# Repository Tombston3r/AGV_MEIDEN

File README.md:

# AGV MEIDEN

Deux chantiers sur le même chariot filoguidé MEIDEN (carte d'origine
`AIO AGV Control V5.0.1`) :

Toutes les architectures suivent la **même chaîne** depuis le 2026-08-28 :

```
Boutons d'appel (optionnels) -> Poste Central -> Carte AGV Control -> AGV
                                API planning
                                appels
```

Les boutons sont **optionnels** : le planning seul fait rouler l'AGV. Les trois
architectures ne diffèrent plus que par la **liaison du poste vers l'AGV** :
[`docs/ARCHITECTURE_COMMUNE.md`](docs/ARCHITECTURE_COMMUNE.md).

| Dossier | Chantier | État |
|---|---|---|
| [`Comm distance/`](Comm%20distance/) | **Remplacement du système d'appel** : 4 architectures étudiées (cellulaire, hybride, LoRa, Wi-Fi), bancs d'essai, matériel KiCad | 470 tests verts, choix client non tranché |
| [`Timer/`](Timer/) | **Planning journalier** : missions déclenchées sur horloge, validation quotidienne par l'opérateur | moteur livré, 18 tests verts |

Chaque chantier porte son `README.md` **et** son `DEPLOY.md`, à quoi ça sert
d'un côté, comment le mettre en service et ce qu'on doit voir de l'autre. La
règle de rangement commune est dans
[`docs/ORGANISATION.md`](docs/ORGANISATION.md) : *tout ce qui sert à une chose
vit avec elle, documentation comprise.*

Toutes les interfaces web du dépôt suivent le **même thème** : fond blanc,
bleu outremer, logo AIO : [`docs/theme/`](docs/theme/), propagé par
`outils/theme.sh`.

Les deux partagent la même carte et le même cœur métier : le Timer produira
ses missions vers le séquenceur déjà écrit dans
[`Comm distance/architectures/A3_Wifi/`](Comm%20distance/architectures/A3_Wifi/).

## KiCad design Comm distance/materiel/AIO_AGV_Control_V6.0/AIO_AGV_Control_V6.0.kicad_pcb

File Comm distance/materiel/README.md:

# Matériel : projets KiCad

**Une carte, un projet, un seul endroit.** Même quand deux architectures
partagent une carte, elle n'est pas dupliquée : trois copies divergentes de la
V6.0 ont déjà coexisté dans ce dépôt, et il a fallu comparer les schémas pour
savoir laquelle portait le travail réel. Un firmware dupliqué se compare par
`diff` ; deux schémas KiCad divergents, non.

| Projet | Sert à | Empreintes | État |
|---|---|---:|---|
| [`AIO_AGV_Control_V5.0.1/`](AIO_AGV_Control_V5.0.1/) | **A3** : Wi-Fi | 57 | carte d'origine, **en service sur le chariot** |
| [`AIO_AGV_Control_V6.0/`](AIO_AGV_Control_V6.0/) | **A2** et **A3** : LoRa | 59 | Gerbers exportés |

## Ce qui distingue la V6.0

Le diff des deux projets ne montre **aucun écart** hors la radio : mêmes
`Mega2560 Pro` et `ESP32-DEVKITC`, mêmes 23 `IRF520` et résistances de grille,
même `L7806CV`, même `TDN 5-2411WISM`, mêmes SUB-D 25.

S'y ajoutent un **`RFM95W-868S2` (U2)** et son **embase coaxiale (J3)**.

### Brochage relevé

| RFM95W | ESP32 |
|---|---|
| `NSS` | `IO5` |
| `SCK` | `IO18` |
| `MISO` | `IO19` |
| `MOSI` | `IO23` |
| `DIO0` | `IO26` |

⚠️ **`RESET` (pad 6) n'est pas connectée.** Aucun reset logiciel n'est possible :
un module figé ne se récupérera qu'en coupant l'alimentation de la carte.
**`IO27` est libre** et conviendrait, sans fonction de strapping au démarrage,
contrairement à `IO0`, `IO2`, `IO12` ou `IO15`.

⚠️ **`IO16` et `IO17` sont réservées** : elles portent la liaison série vers le
`Mega2560 Pro`, via un pont diviseur 2,2 k / 4,7 k dans le sens 5 V → 3,3 V.

## Points relevés sur la V5.0.1, valables pour les deux

- **Les trois UART matériels du MEGA sont inutilisables** : leurs broches de
  réception portent `Y13` (D19), `Y11` (D17) et `Y05` (D15). La liaison
  inter-microcontrôleurs est en `SoftwareSerial` sur D52/D53, à 38 400 bauds.
- **L'`IRF520` n'est pas un MOSFET logic-level** : seuil spécifié de 2 à 4 V,
  `Rds(on)` garanti à Vgs = 10 V. Attaqué en 5 V il conduit, mais hors des
  conditions du constructeur. L'`IRL520N` est la version logic-level **au même
  brochage**.
- **Les 21 entrées Y arrivent directement sur les broches de l'ATmega**, sans
  protection. Le client a vérifié que les niveaux le permettent.

Le relevé complet du câblage SUB-D vit dans
[`../architectures/A3_Wifi/docs/subd25_atmega.md`](../architectures/A3_Wifi/docs/subd25_atmega.md).

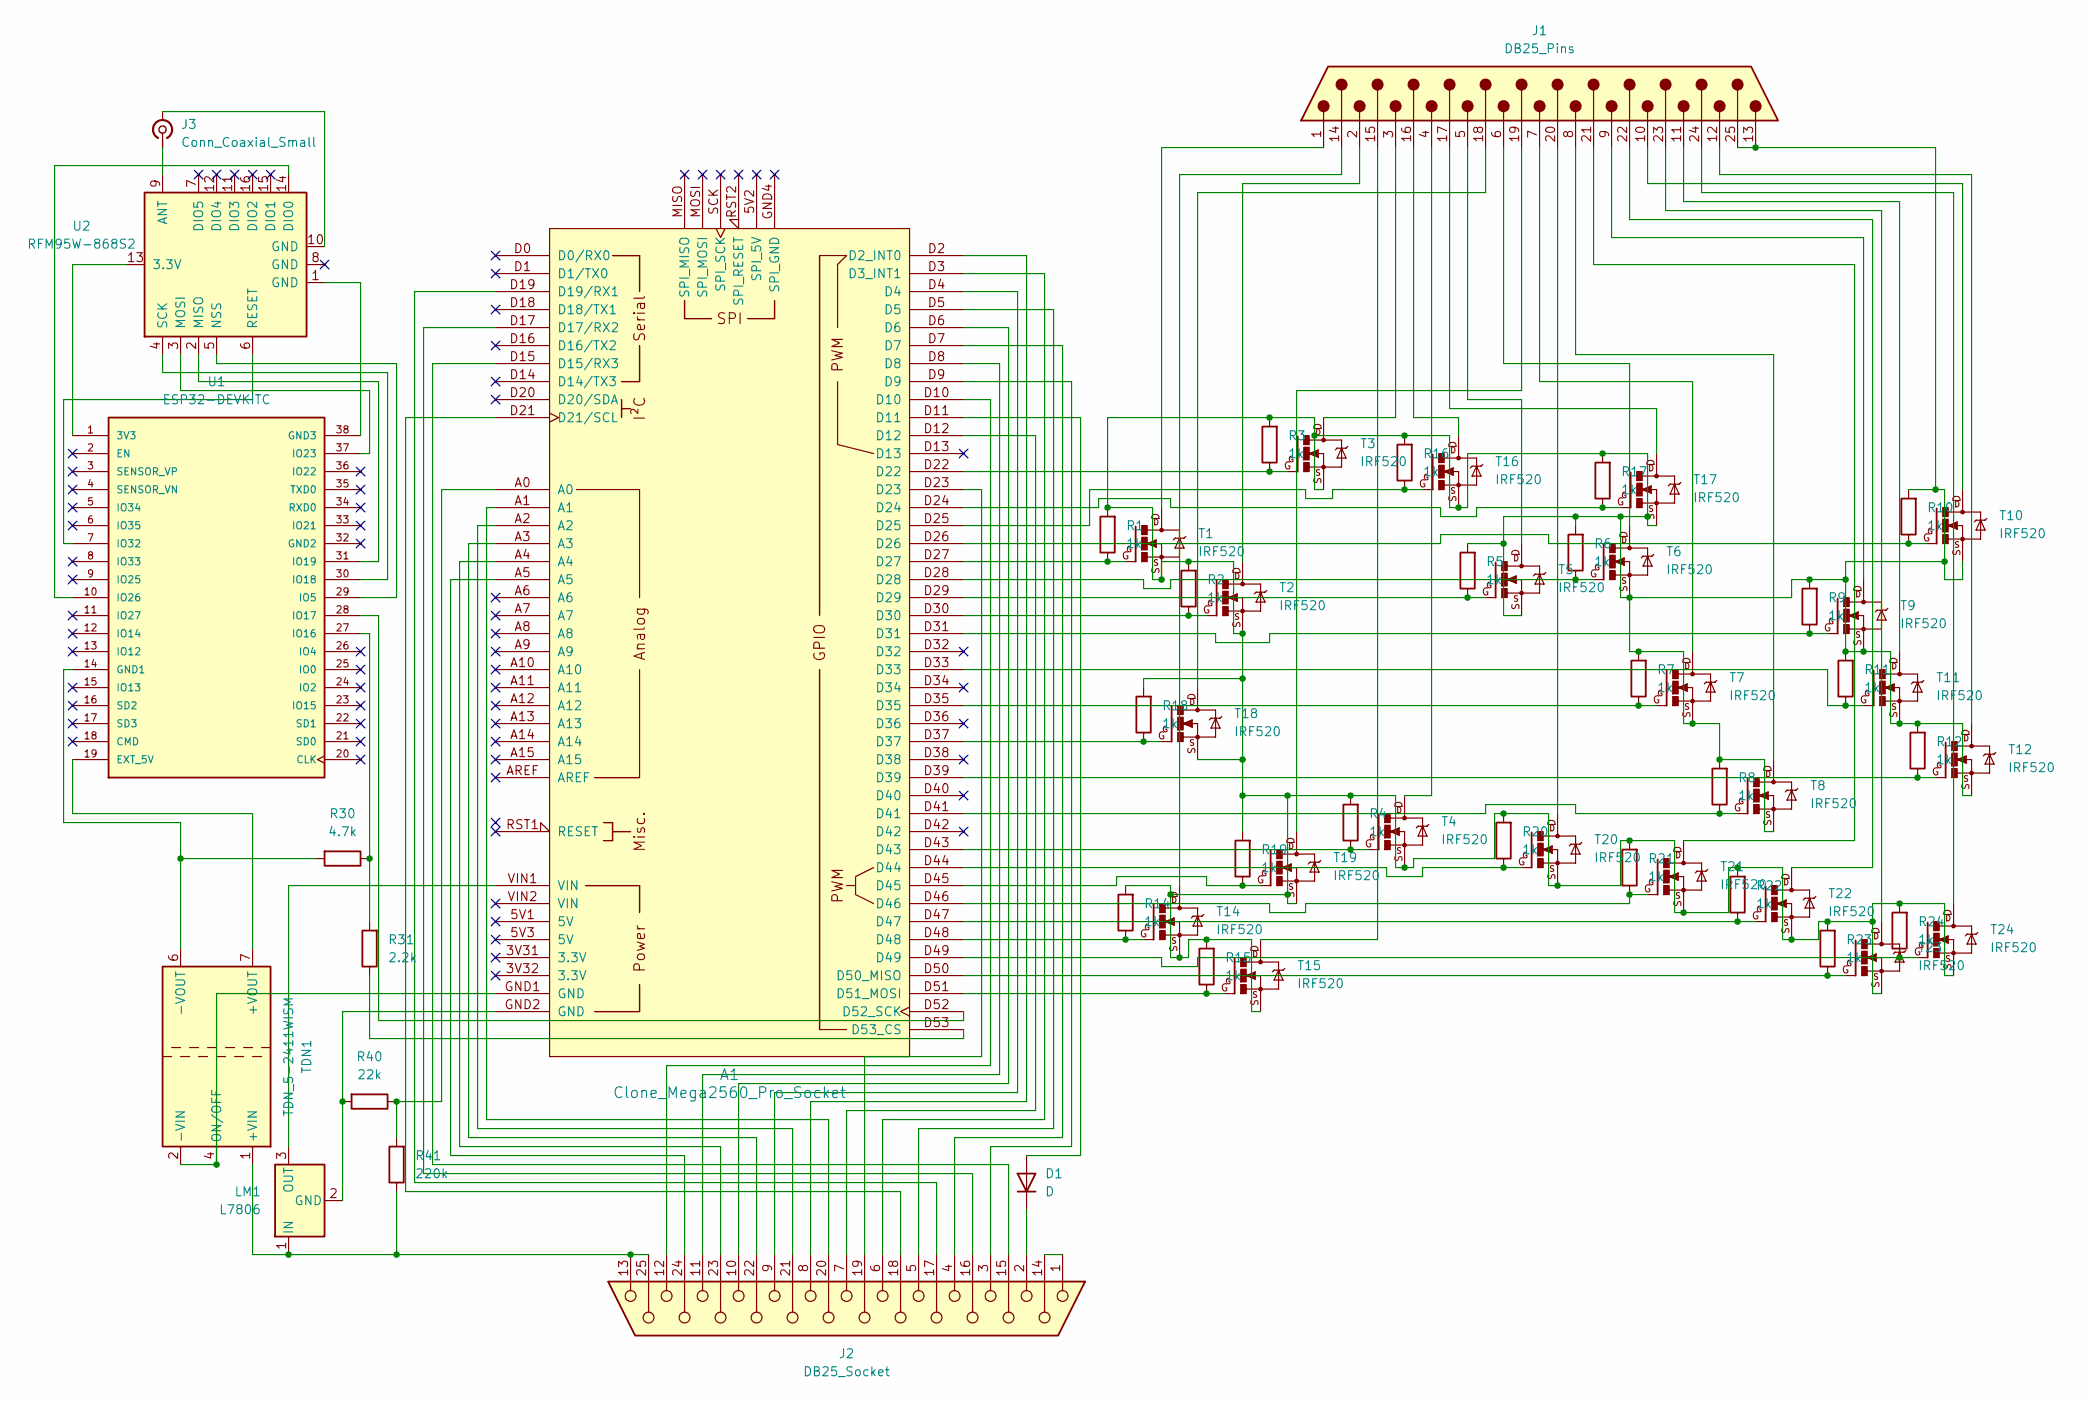
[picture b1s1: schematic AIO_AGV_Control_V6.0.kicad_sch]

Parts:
A1: Clone_Mega2560_Pro_Socket
D1: D; D_DO-41_SOD81_P10.16mm_Horizontal
J1: DB25_Pins; AMPHENOL_DB25P564CTXLF
J2: DB25_Socket; AMPHENOL_DB25S564GTLF
J3: Conn_Coaxial_Small; SMA_Amphenol_901-143_Horizontal
LM1: L7806; TO255P1020X450X1968-3B
R1, R2, R3, R4, R5, R6, R7, R8, R9, R10, R11, R12, R14, R15, R16, R17, R18, R19, R20, R21, R22, R23, R24: 1k; R_Axial_DIN0411_L9.9mm_D3.6mm_P12.70mm_Horizontal
R30: 4.7k; R_Axial_DIN0411_L9.9mm_D3.6mm_P12.70mm_Horizontal
R31: 2.2k; R_Axial_DIN0411_L9.9mm_D3.6mm_P12.70mm_Horizontal
R40: 22k; R_Axial_DIN0411_L9.9mm_D3.6mm_P12.70mm_Horizontal
R41: 220k; R_Axial_DIN0411_L9.9mm_D3.6mm_P12.70mm_Horizontal
T1, T2, T3, T4, T5, T6, T7, T8, T9, T10, T11, T12, T14, T15, T16, T17, T18, T19, T20, T21, T22, T23, T24: IRF520; TO220BV
TDN1: TDN_5-2411WISM; Converter_DCDC_TRACO_TDN_5-xxxxWISM_SMD
U1: ESP32-DEVKITC; MODULE_ESP32-DEVKITC; PARTREV N/A
U2: RFM95W-868S2; HOPERF_RFM9XW_SMD

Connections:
unnamed: A1.D2 (D2_INT0), J2.8
unnamed: A1.D3 (D3_INT1), J2.6
unnamed: A1.D15 (D15/RX3), J2.15
unnamed: A1.D17 (D17/RX2), J2.16
unnamed: A1.D19 (D19/RX1), J2.17
unnamed: A1.D21 (D21/SCL), J2.18
unnamed: A1.D50 (D50_MISO), R23.1, T23.G
unnamed: A1.D51 (D51_MOSI), R15.1, T15.G
unnamed: A1.D52 (D52_SCK), U1.28 (IO17)
unnamed: A1.D53 (D53_CS), R31.1
unnamed: A1.A0, R40.1, R41.2
unnamed: A1.D4, J2.9
unnamed: A1.D5, J2.5
unnamed: A1.D6, J2.10
unnamed: A1.D7, J2.4
unnamed: A1.D8, J2.11
unnamed: A1.D9, J2.3
unnamed: A1.D10, J2.12
unnamed: A1.D12, J2.7
unnamed: A1.D22, R3.1, T3.G
unnamed: A1.D24, R17.1, T17.G
unnamed: A1.D25, R16.1, T16.G
unnamed: A1.D26, R10.1, T10.G
unnamed: A1.D27, R1.1, T1.G
unnamed: A1.D28, R6.1, T6.G
unnamed: A1.D29, R5.1, T5.G
unnamed: A1.D30, R2.1, T2.G
unnamed: A1.D31, R9.1, T9.G
unnamed: A1.D33, R11.1, T11.G
unnamed: A1.D35, R7.1, T7.G
unnamed: A1.D37, R18.1, T18.G
unnamed: A1.D39, R12.1, T12.G
unnamed: A1.D41, R8.1, T8.G
unnamed: A1.D43, R4.1, T4.G
unnamed: A1.D44, R20.1, T20.G
unnamed: A1.D45, R19.1, T19.G
unnamed: A1.D46, R21.1, T21.G
unnamed: A1.D47, R22.1, T22.G
unnamed: A1.D48, R14.1, T14.G
unnamed: A1.D49, R24.1, T24.G
unnamed: A1.D11, D1.2 (A)
unnamed: D1.1 (K), J2.2
unnamed: J1.14, T14.D
unnamed: J1.15, T15.D
unnamed: J1.16, T16.D
unnamed: J1.17, T17.D
unnamed: J1.18, T18.D
unnamed: J1.19, T19.D
unnamed: J1.20, T20.D
unnamed: J1.21, T21.D
unnamed: J1.22, T22.D
unnamed: J1.23, T23.D
unnamed: J1.24, T24.D
unnamed: J1.13, J1.25, R1.2, R2.2, R3.2, R4.2, R5.2, R6.2, R7.2, R8.2, R9.2, R10.2, R11.2, R12.2, R14.2, R15.2, R16.2, R17.2, R18.2, R19.2, R20.2, R21.2, R22.2, R23.2, R24.2, T1.S, T2.S, T3.S, T4.S, T5.S, T6.S, T7.S, T8.S, T9.S, T10.S, T11.S, T12.S, T14.S, T15.S, T16.S, T17.S, T18.S, T19.S, T20.S, T21.S, T22.S, T23.S, T24.S
unnamed: J1.1, T1.D
unnamed: J1.2, T2.D
unnamed: J1.3, T3.D
unnamed: J1.4, T4.D
unnamed: J1.5, T5.D
unnamed: J1.6, T6.D
unnamed: J1.7, T7.D
unnamed: J1.8, T8.D
unnamed: J1.9, T9.D
unnamed: J1.10, T10.D
unnamed: J1.11, T11.D
unnamed: J1.12, T12.D
unnamed: J2.1, J2.14
unnamed: A1.D23, J2.19
unnamed: A1.A1, J2.20
unnamed: A1.A2, J2.21
unnamed: A1.A3, J2.22
unnamed: A1.A4, J2.23
unnamed: A1.A5, J2.24
unnamed: J2.13, J2.25, LM1.1 (IN), R41.1, TDN1.1 (+VIN)
unnamed: J3.2 (Ext), U2.10 (GND)
unnamed: J3.1 (In), U2.9 (ANT)
unnamed: A1.GND2 (GND), LM1.2 (GND), R40.2
unnamed: A1.VIN1 (VIN), LM1.3 (OUT)
unnamed: TDN1.7 (+VOUT), U1.19 (EXT_5V)
unnamed: A1.GND1 (GND), TDN1.2 (-VIN), TDN1.4 (ON/OFF)
unnamed: R30.2, TDN1.6 (-VOUT), U1.14 (GND1)
unnamed: U1.1 (3V3), U2.13 (3.3V)
unnamed: U1.38 (GND3), U2.1 (GND)
unnamed: U1.29 (IO5), U2.5 (NSS)
unnamed: R30.1, R31.2, U1.27 (IO16)
unnamed: U1.30 (IO18), U2.4 (SCK)
unnamed: U1.31 (IO19), U2.2 (MISO)
unnamed: U1.37 (IO23), U2.3 (MOSI)
unnamed: U1.10 (IO26), U2.14 (DIO0)
unnamed: U1.7 (IO32), U2.6 (RESET)

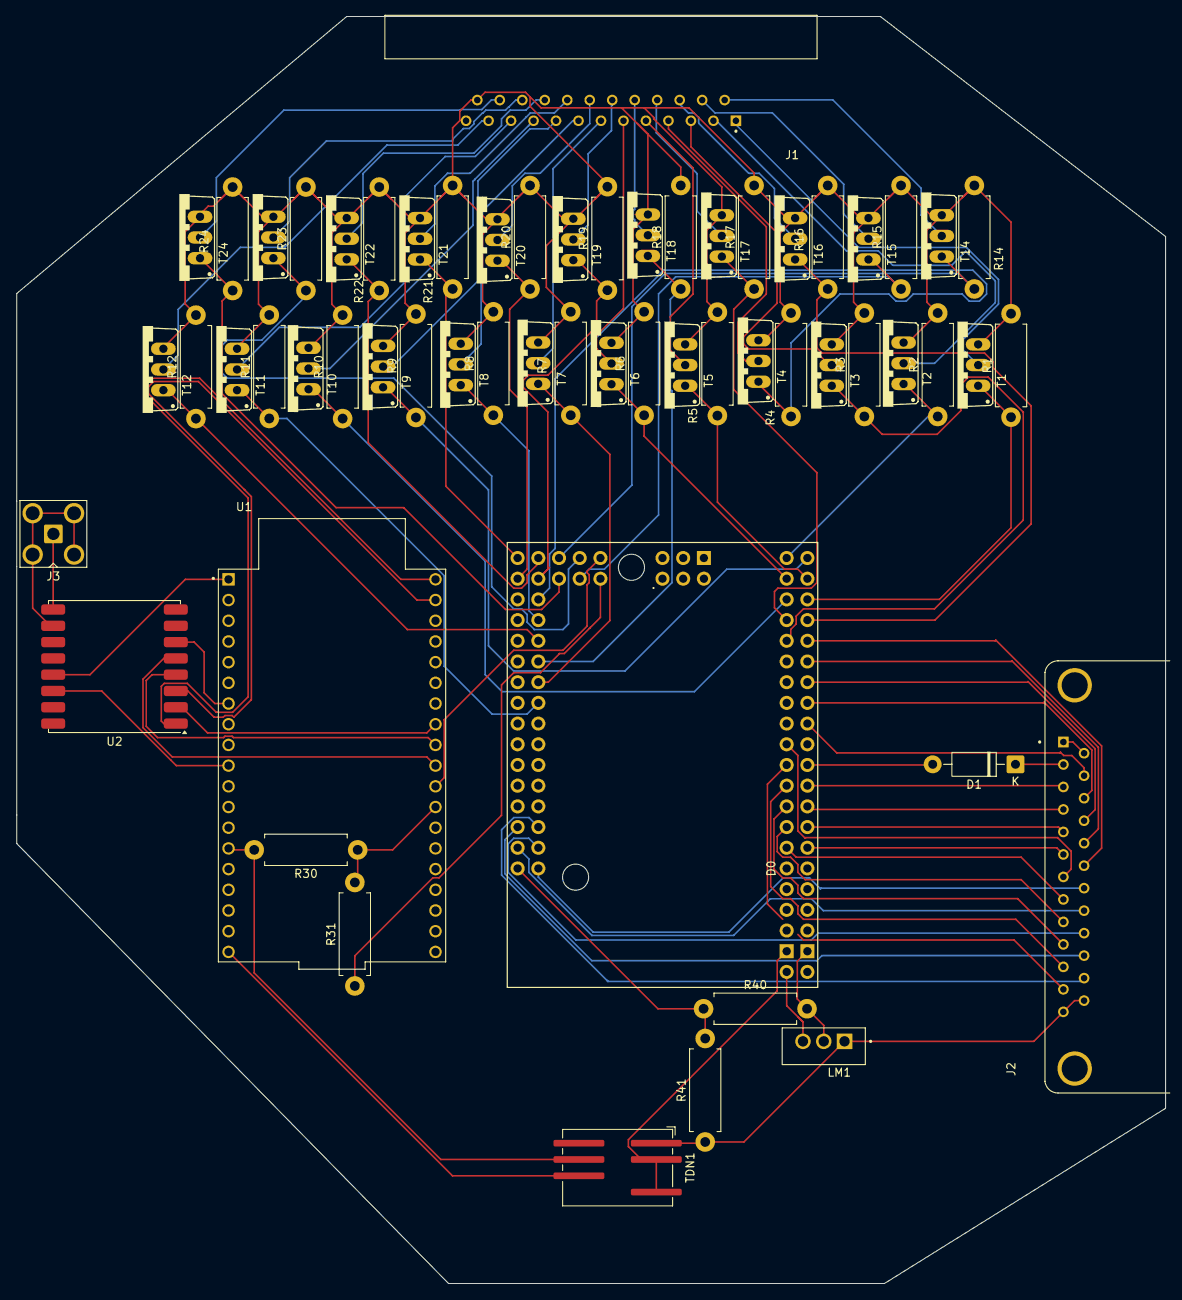
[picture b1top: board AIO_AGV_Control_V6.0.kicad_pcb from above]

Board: 2 copper layers, 141.0 x 155.5 mm, 59 parts (0 on the bottom side), 90 nets.
